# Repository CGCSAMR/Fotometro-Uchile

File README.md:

Fotometro-Uchile
================

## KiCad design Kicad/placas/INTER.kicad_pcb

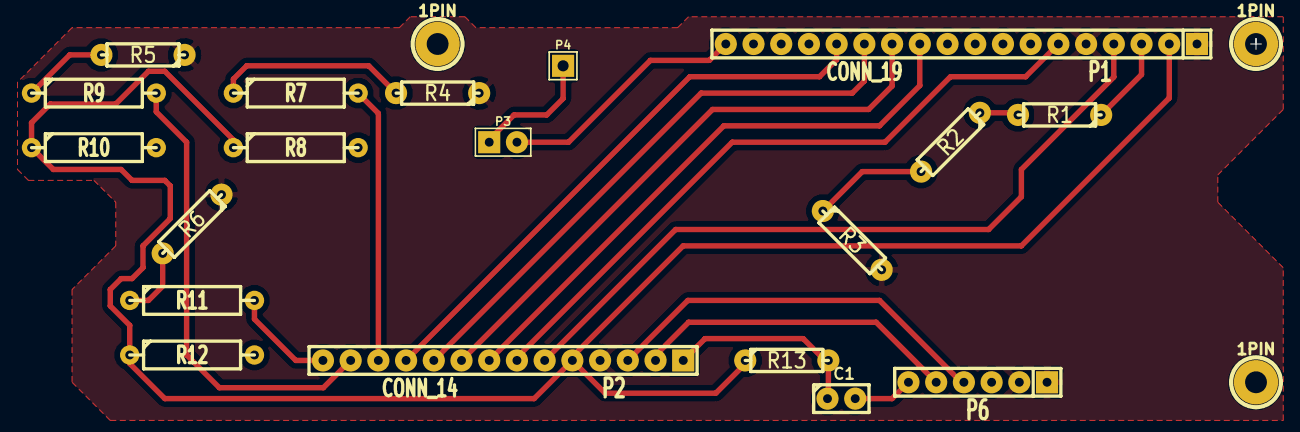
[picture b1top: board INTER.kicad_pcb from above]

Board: 2 copper layers, 22 parts (0 on the bottom side), 23 nets.

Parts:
1PIN, 1PIN#2, 1PIN#3: P***; 1pin
C1: 0.1 uF; C1
P1: CONN_19; SIL-18
P2: CONN_14; SIL-14
P3: CONN_2; PIN_ARRAY_2X1
P4: CONN_1; PIN_ARRAY_1
P6: CONN_6; SIL-6
R1, R2: 1K; R3-LARGE_PADS
R3: 22 Omn; R3-LARGE_PADS
R4, R5, R6, R13: 10K; R3-LARGE_PADS
R7, R8, R9, R10, R11, R12: BTN; R4-5

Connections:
+5V: P1.2, P2.5, R8.1, R10.1, R12.1, R13.1
/2: P1.14, P2.11
/3: P1.13, P2.10
/4: P1.12, P2.9
/6: P1.11, P2.8
/7: P2.12, R7.2
/9: P1.4, P2.6
/10: P1.6, P2.7
/A2: P2.14, R11.2
/A3: P2.13, R9.2
/BAT: P1.18, P3.2
/DTR: C1.2, P6.6
/R: P1.3, R1.1
/RST: C1.1, P2.1, R13.2
/RX0: P2.2, P6.5
/TX1: P2.3, P6.4
/Vin: P3.1, P4.1
GND: P1.1, P1.5, P2.4, P6.1, P6.2, R3.2, R4.1, R5.1, R6.1
unnamed: R6.2, R11.1
unnamed: R4.2, R7.1
unnamed: R2.2, R3.1
unnamed: R1.2, R2.1
unnamed: R5.2, R9.1

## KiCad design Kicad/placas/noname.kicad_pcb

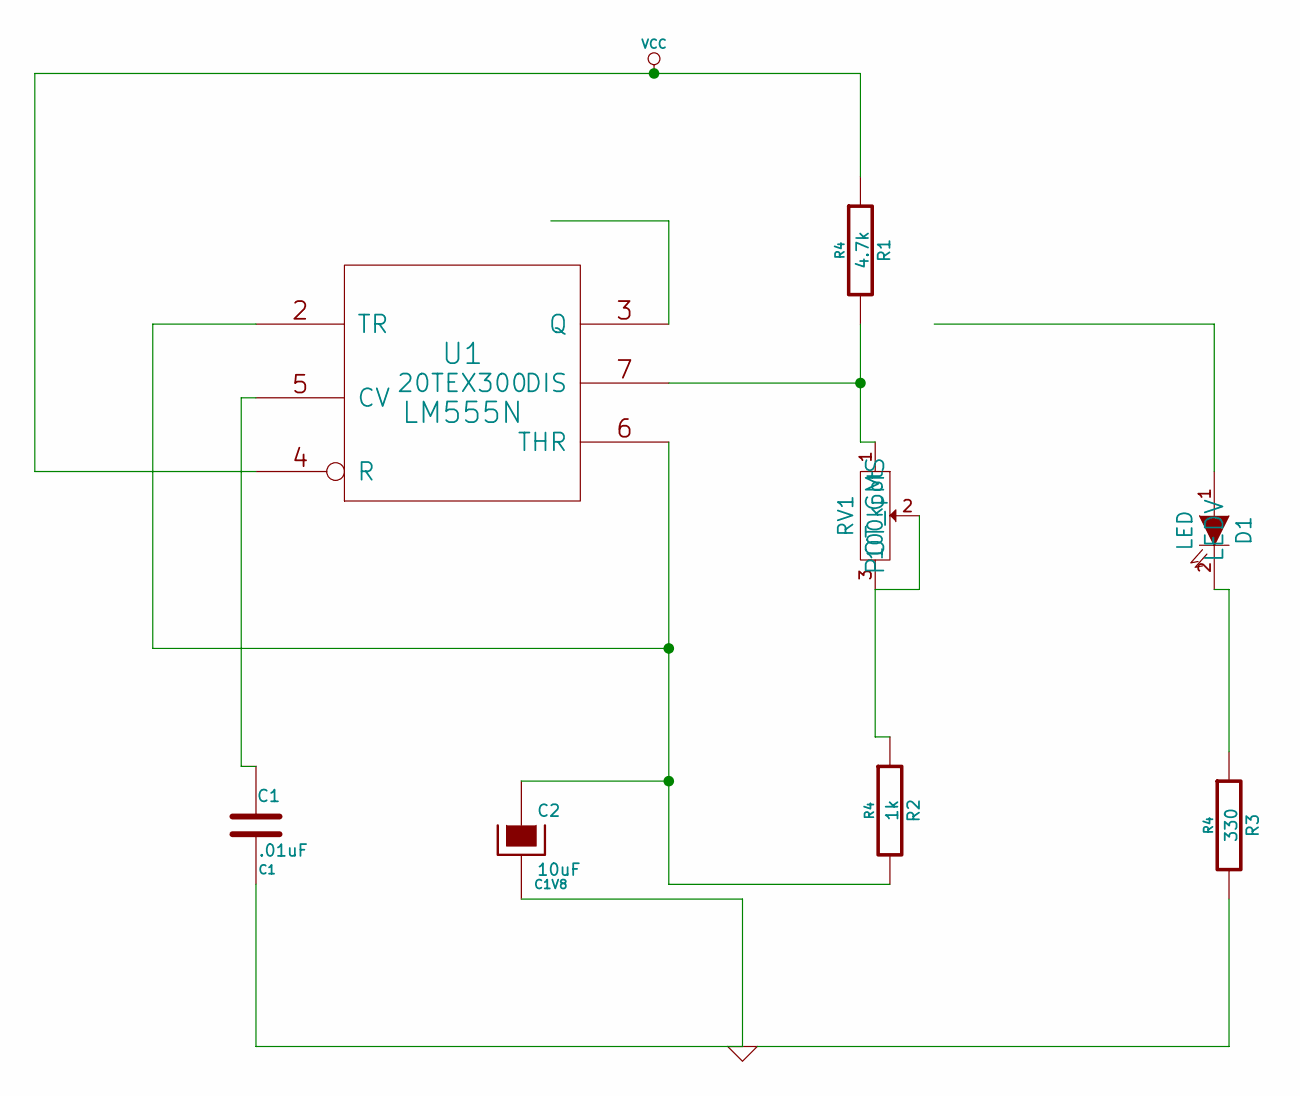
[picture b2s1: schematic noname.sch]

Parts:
C1: .01uF; C1
C2: 10uF; C1V8
D1: LED; LEDV
R1: 4.7k; R4
R2: 1k; R4
R3: 330; R4
RV1: 100kpot; POT_CMS
U1: LM555N; 20TEX300

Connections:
GND: C1.2, C2.2, U1.1 (GND)
unnamed: C1.1, U1.5 (CV)
unnamed: C2.1, R2.2, U1.2 (TR), U1.6 (THR)
unnamed: R2.1, RV1.2, RV1.3
unnamed: D1.2 (K), R3.1
unnamed: R1.2, RV1.1, U1.7 (DIS)
VCC: R1.1, U1.4 (R), U1.8 (VCC)

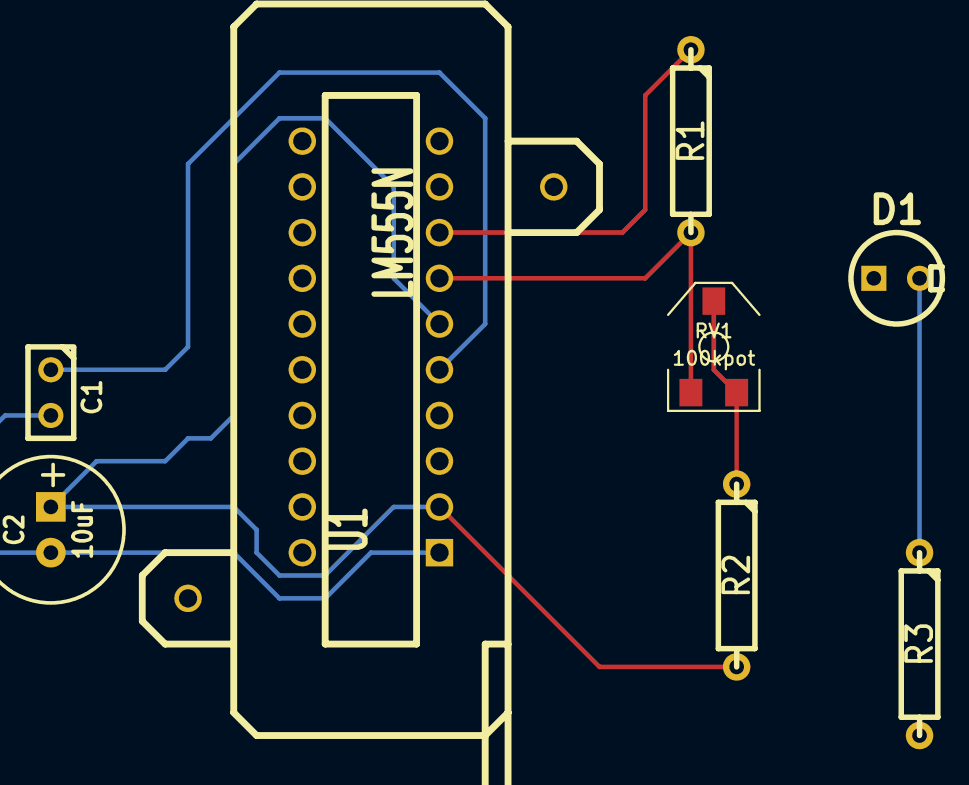
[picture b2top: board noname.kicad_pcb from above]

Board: 2 copper layers, 8 parts (0 on the bottom side), 7 nets.

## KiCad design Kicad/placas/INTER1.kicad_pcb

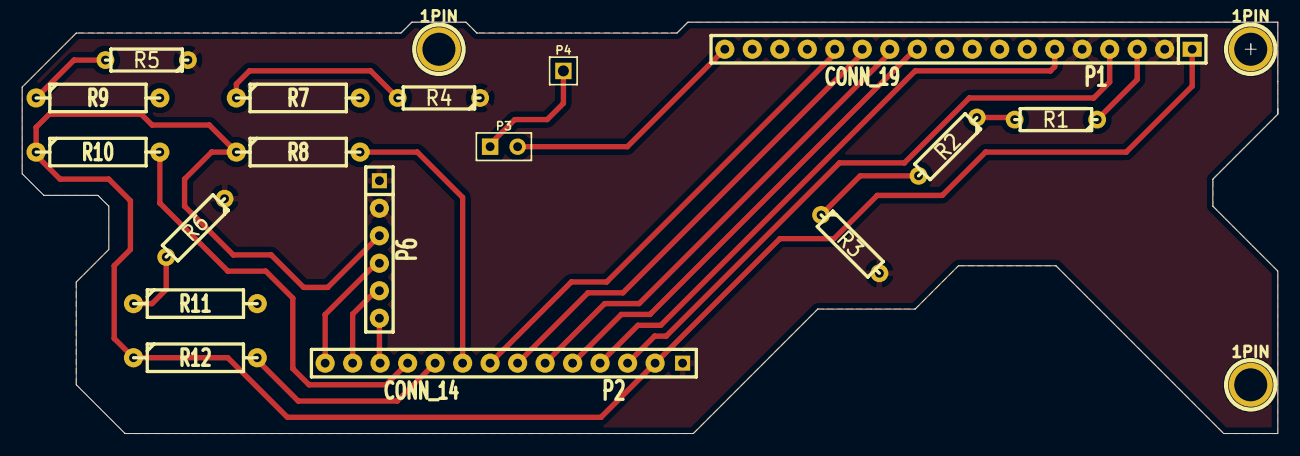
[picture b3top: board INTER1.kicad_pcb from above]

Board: 2 copper layers, 116.0 x 38.0 mm, 20 parts (0 on the bottom side), 22 nets.

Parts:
1PIN, 1PIN#2, 1PIN#3: P***; 1pin
P1: CONN_19; SIL-18
P2: CONN_14; SIL-14
P3: CONN_2; PIN_ARRAY_2X1
P4: CONN_1; PIN_ARRAY_1
P6: CONN_6; SIL-6
R1, R2, R3, R4, R5, R6: R; R3-LARGE_PADS
R7, R8, R9, R10, R11, R12: R; R4-5

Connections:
+5V: P1.1, P2.2, P6.3, R8.1, R10.1, R12.1
/2: P1.14, P2.8
/3: P1.13, P2.7
/4: P1.12, P2.6
/6: P1.11, P2.5
/7: P2.9, R8.2
/9: P1.4, P2.3
/10: P1.6, P2.4
/A2: P2.10, R12.2
/A3: P2.11, R10.2
/BAT: P1.18, P3.2
/R: P1.3, R1.1
/RST: P2.12, P6.6
/RX1: P2.13, P6.5
/TX0: P2.14, P6.4
/Vin: P3.1, P4.1
GND: P1.2, P1.5, P2.1, P6.1, P6.2, R3.2, R4.1, R5.1, R6.1
unnamed: R6.2, R11.1
unnamed: R4.2, R7.1
unnamed: R2.2, R3.1
unnamed: R1.2, R2.1
unnamed: R5.2, R9.1

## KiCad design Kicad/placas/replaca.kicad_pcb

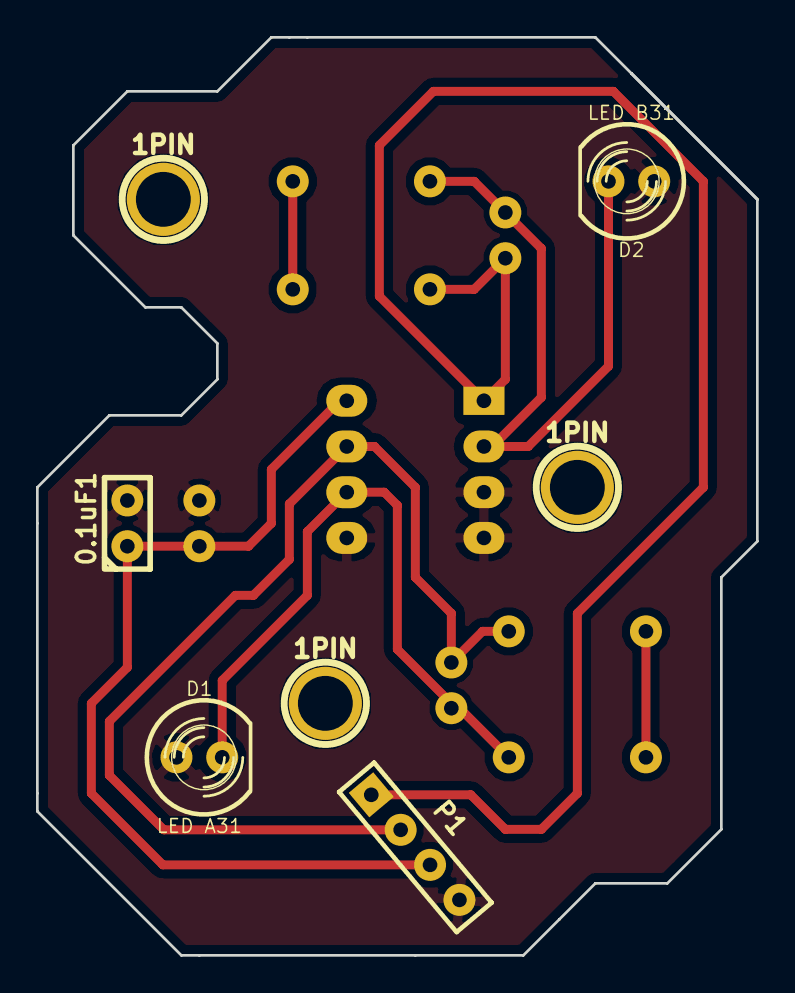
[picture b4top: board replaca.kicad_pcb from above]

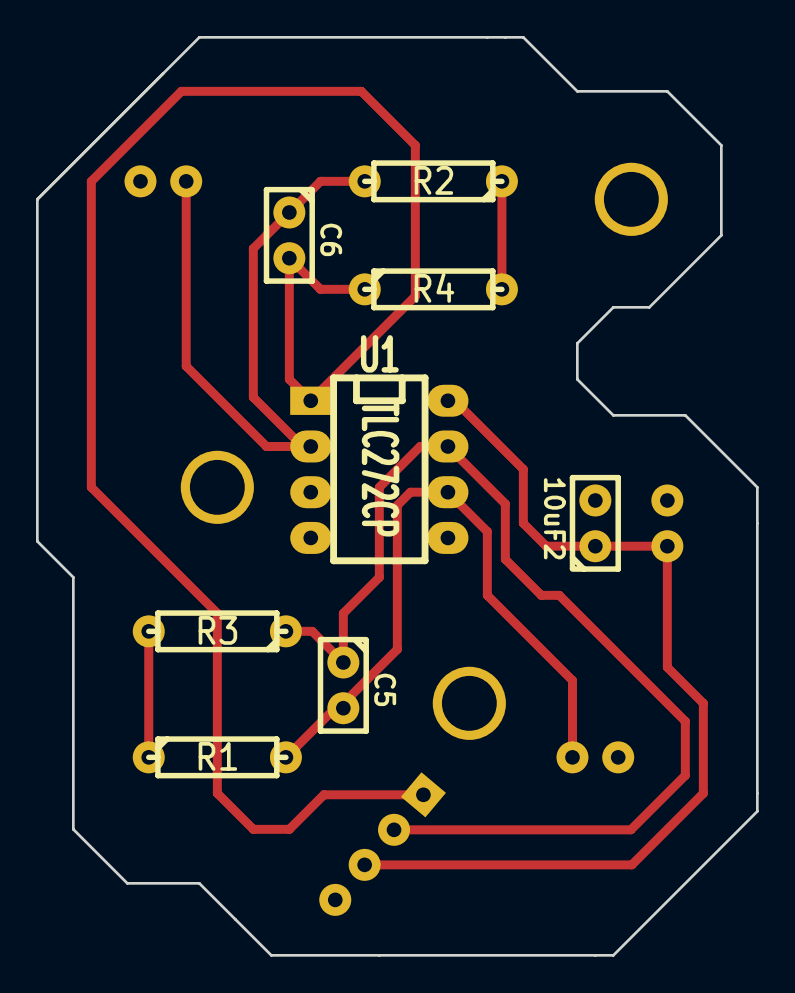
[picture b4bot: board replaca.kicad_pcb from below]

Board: 2 copper layers, 40.0 x 51.0 mm, 15 parts (8 on the bottom side), 8 nets.

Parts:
0.1uF1: C1
1PIN, 1PIN#2, 1PIN#3: P***; 1pin
10uF2: CP1; C1
C5, C6: 0.1uF; C1
D1: LED A31; LED-5MM
D2: LED B31; LED-5MM
P1: CONN_4; PIN_ARRAY_4x1
R1, R2, R3, R4: R; R3-LARGE_PADS
U1: TLC272CP; DIP-8__300_ELL

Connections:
+5V: 0.1uF1.1, 10uF2.1, P1.3, U1.8
/2: C6.1, D2.2, R2.2, U1.2
/6: C5.2, D1.2, R1.2, U1.6
/A1: C6.2, P1.1, R4.1, U1.1
/A2: C5.1, P1.2, R3.1, U1.7
GND: 0.1uF1.2, 10uF2.2, D1.1, D2.1, P1.4, U1.3, U1.4, U1.5
unnamed: R2.1, R4.2
unnamed: R1.1, R3.2

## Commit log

2014-01-07 Planos estructurales
    algunas versiones (sin ordenar)
2014-01-07 más cambios
2014-01-08 Alguno cambios, próximamente, muchos más
    :):)
2014-01-09 Placas electronicas
2014-01-09 Más modificaciones a los planos
    yei
2014-01-09 Ultima de la noche
    Falta tabiques del anclaje y determinar ubicación de pantalla
2014-01-09 Agregado espacio para pantalla LCD
    recordar que es el mínimo posible, luego todo el circuito seráfuera de
    la carcasa
2014-01-09 Plano terminados
2014-01-09 Planos Corregidos y STL para imprimir
2014-01-14 Codigo Arduino con librerias correspondientes
2014-01-14 Mira provisoria
2014-01-14 más piezas
2014-01-16 modificación pequeña
2014-01-16 dolar
2014-01-16 piezas para la versión final
2014-01-16 ediciones de prueba
2014-01-16 no se
2014-01-16 modificaciones en vivo
2014-01-17 modificaciones para versión release
2014-01-17 un detalle
2014-01-18 planos casi definitivos
2014-01-20 más detalles
    agujeros para nueva placa para interfaz.
2014-01-23 Ultimo ensamblaje
2014-01-26 cambios varios
2014-01-26 ultimo caso
2014-02-21 modificaciones convergentes
2014-02-26 interfas
2014-02-26 I have no Idea
2014-02-27 eh..
2014-02-27 doble pressure repair
2014-02-28 Da Ba Dee
2014-03-01 Correciones SW2014
2014-05-16 Adaptador Tipo A modificado
    Usese SW 2013 en adelante, falta hacer molde
2014-07-14 Cambios al digivice
2014-07-15 Nuevo agujero en el soporte
2014-07-15 Retoque digivice
2014-07-21 STL nuevas modificaciones
2014-07-22 Apagando el fuego con bencina
    Rescate de la borrada rama Kfop (QEPD) :(
2014-07-22 Sigue el cuento
2014-07-22 Arreglo versión pseudo-estable
    Orden et orbi
2014-07-23 Corregido archivo "DateStrings.cpp" de libreria Time
2014-07-25 Modificaciones Faltantes
    Falta el molde
2014-07-31 Se inicia trabajo del nuevo programa del fotometro en Git
2014-07-31 Created LightSensor library v0.1
2014-07-31 Fixed bugs in LightSensor library, now it should compile
2014-08-01 Reubicación piezas inútiles siguiente fase
2014-08-02 Arreglo dado éxito
2014-08-05 ultimas mejoras
2014-08-20 Nuevo formato de orden, espero sea más comodo
2014-08-21 retracto
2014-08-22 fixed names
2014-08-22 We come back!
2014-08-22 ahora si
2014-08-23 Agregadas placas completas
    Sin arreglar
2014-10-14 Se agrega ondemandMax
2014-10-14 Arreglar ondemandMax
2014-10-16 added pysolar
2014-10-30 Se anota valores de resistencias para pre-calibracion
2014-10-30 Reloj fotometro
2015-01-06 fixed DataloggerAtmosfera4_2_Lite to be read by MATLAB, now stable ver is DataloggerAtmosfera4_3_Lite
2015-01-06 Added MATLAB-like script
2015-01-09 Se abre carpeta de C
2015-01-12 Cimel Math Scripts
2015-01-12 CIMEL tiene todos los scripts Math para interpretar medición
2015-01-12 Objetivos a programar en C
2015-01-14 Contabilidad
    Subí la contabilidad actual.
2015-01-14 Actualizada última boleta 14-enero
2015-01-15 Boletas agregadas
2015-01-15 Datalogger 4_3 lite actualizado
2015-01-15 Datalogger 4_3 lite retardo corregido
2015-01-15 Agregar pantalla a programa de medicion
2015-01-16 Agregadas las entregas
2015-01-16 Lector datos Aeronet
2015-01-16 Se elimina calculo de varianza, se mide solo maximo. Un-tested
2015-01-16 Observaciones para futura documentación
2015-01-16 Math y Arduino actualizados
2015-01-19 Nueva version de programa tratamiento de datos
2015-01-19 Se agrego funcion sun_position modificada
2015-01-19 minor updates
2015-01-19 se agregaron long. onda eq. tentativas
2015-01-19 programa de AOT listo, falta corregir long. de onda
2015-01-19 Arreglado formato de archivo de salida
2015-01-19 Para extraer los documentos I
2015-01-19 Para extraer los documentos II
2015-01-20 Extraccion de datos y calculo de AOT Fotometro Calan estable
2015-01-20 Se agregan longitudes de onda eq correctas
2015-01-20 nada
2015-01-20 nuevo formato de datos
2015-01-20 estable
2015-01-20 Fusión
2015-01-20 version 20 enero
2015-01-20 Versiones U
2015-01-21 Problemas es la respuesta
    versión inestable y reembolsos
2015-01-22 version 22 enero 2015
2015-01-23 DatosCalibracion
2015-01-23 Datos para graficos
2015-01-28 mediciones san cristobal
2015-01-29 contabilidad actualizada
2015-01-29 OPtiMac
2015-01-29 matlab
2015-01-29 Arreglado OnDemandMax, viva el comandante Chavez!
2015-01-30 Programa realizado de optimización
2015-02-02 52 actualizaciones!!
2015-02-10 Función filtro
    7 sensor azul, 8 sensor rojo
2015-02-10 más fix
2015-02-10 datos la parva
2015-02-10 data falvey fix
2015-02-10 procesamiento langley plot
2015-02-11 Documentos calibracion
2015-02-11 actualizacion a ultima version
2015-03-11 Datos previos campana calibracion
2015-03-12 Documentos filtrados
    revisar archivos data_'fotometro'_30.csv
2015-03-13 Calibracion de febrero incorporada
2015-05-16 Codigo para el experimento de calibracion por temperatura
2015-05-16 actualizacion
2015-05-17 version previa viaje a conce
2015-06-19 ultima version estable lite 4_5_lite
2015-06-19 Added stable version
2015-07-09 Se agrega calibracion
2015-07-11 Correccion calibracion
2016-04-27 Reordenamiento
